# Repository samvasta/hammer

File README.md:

# Hammer

It is tradition for blacksmiths to build their own tools.

In building their tool set, the smith practices their craft and gains a deeper understanding of each tool - what went into its production, how and why it functions. The smith's hammer is built to fit the smith's hands and meet their needs exactly.

The smith's hammer may not make them a better smith, but does make their craft more enjoyable.

I am not a smith, I am a programmer. I work with keyboards and this *my* hammer.

---

This repository contains information about the *hardware*. There may be several different branches to support variations of the hammer.

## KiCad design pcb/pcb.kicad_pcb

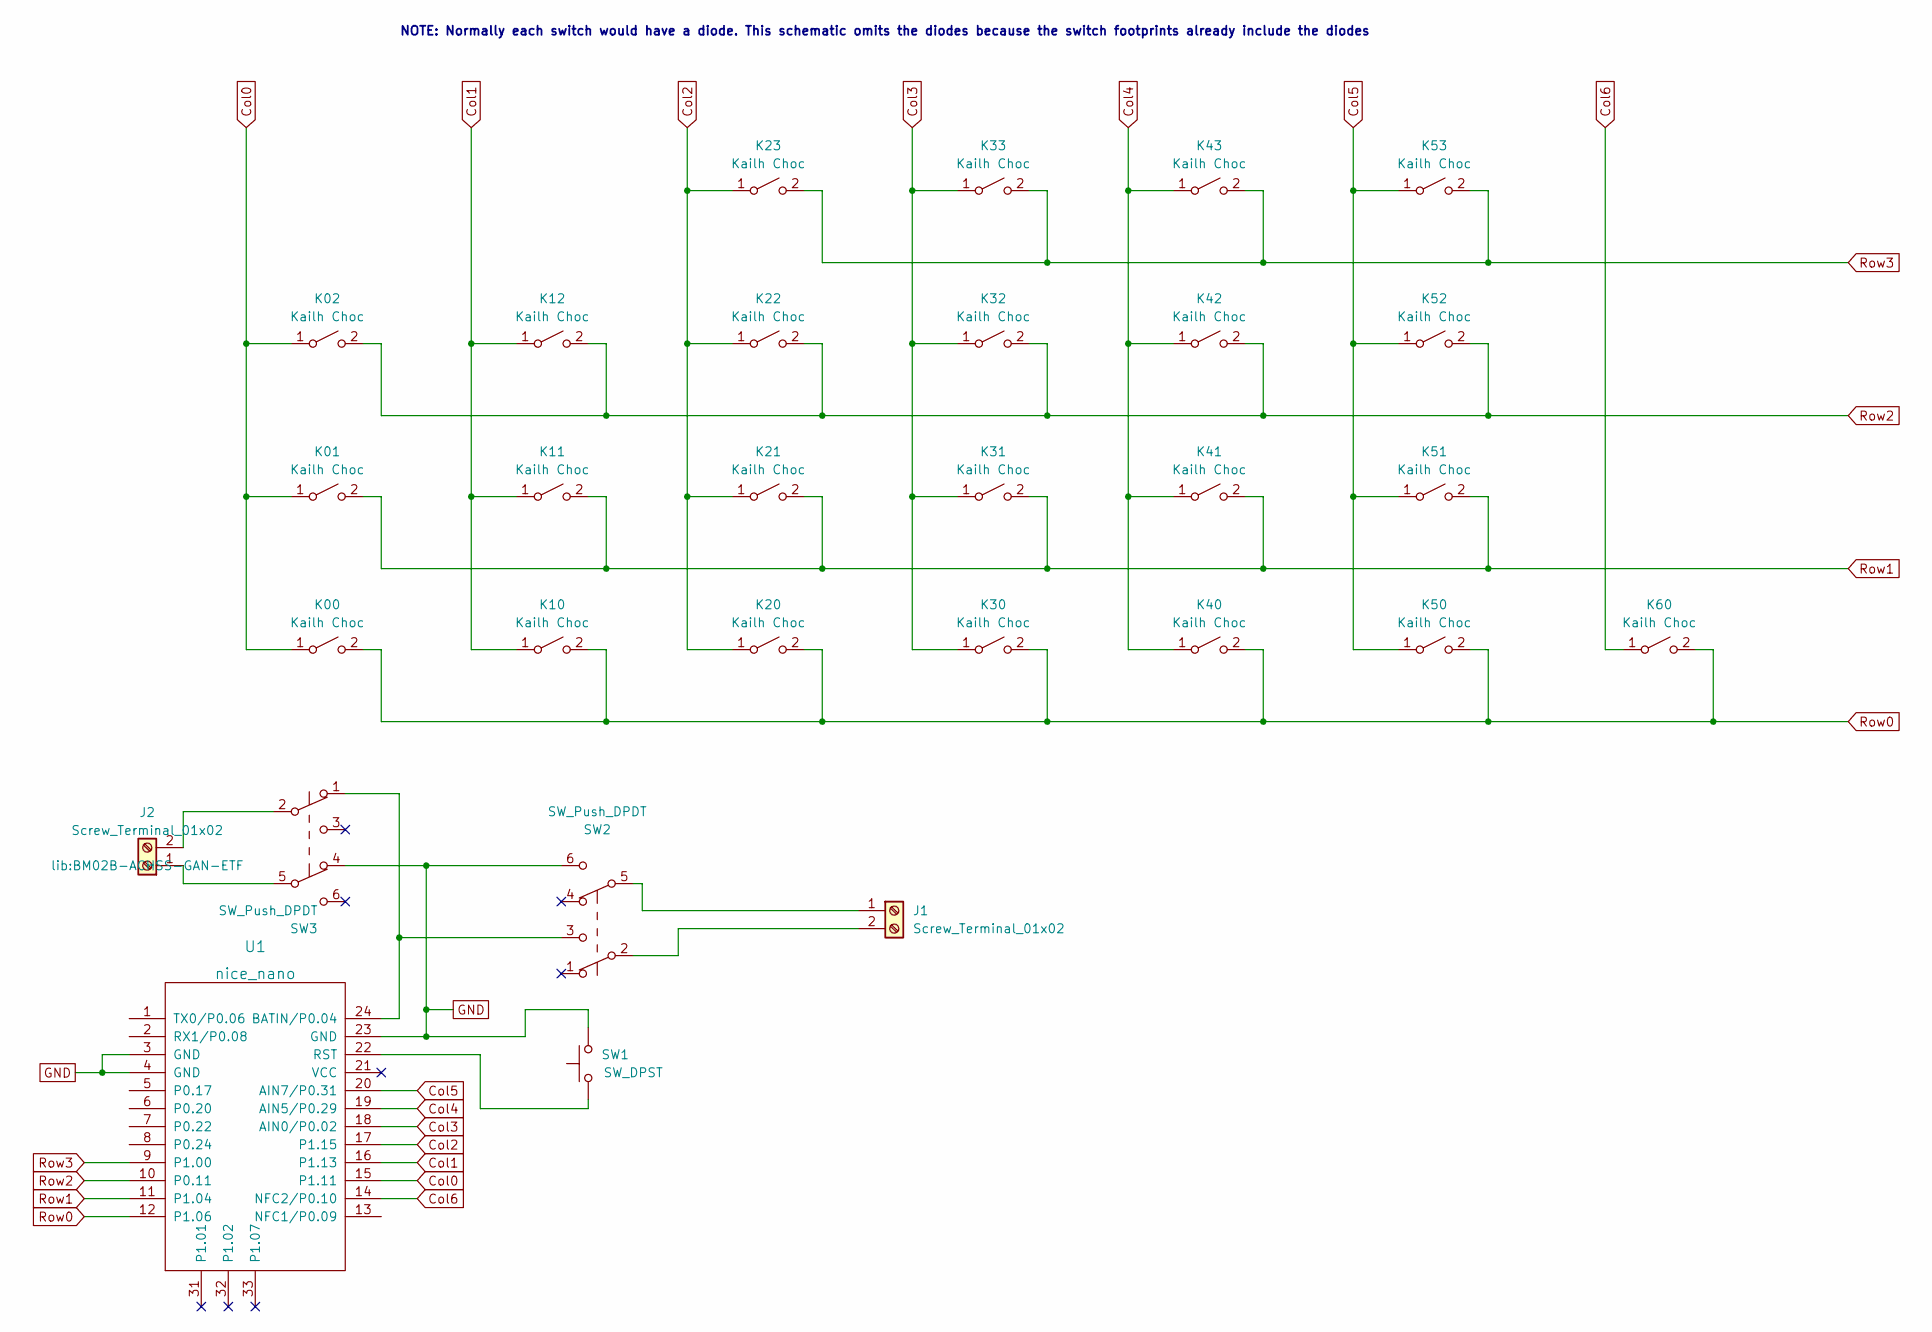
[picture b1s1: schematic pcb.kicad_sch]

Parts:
J1, J2: Screw_Terminal_01x02; BM02B-ACHSS-GAN-ETF
K00, K01, K02, K10, K11, K12, K20, K21, K22, K23, K30, K31, K32, K33, K40, K41, K42, K43, K50, K51, K52, K53, K60: Kailh Choc; Kailh_socket_PG1350_reversible
SW1: SW_DPST; SW_PUSH_6mm
SW2, SW3: SW_Push_DPDT; SW_JS202011SCQN (Reverse Mount)
U1: nice_nano; DIP-24_W15.24mm_Socket

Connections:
Col0: K00.1 (A), K01.1 (A), K02.1 (A), U1.15 (P1.11)
Col1: K10.1 (A), K11.1 (A), K12.1 (A), U1.16 (P1.13)
Col2: K20.1 (A), K21.1 (A), K22.1 (A), K23.1 (A), U1.17 (P1.15)
Col3: K30.1 (A), K31.1 (A), K32.1 (A), K33.1 (A), U1.18 (AIN0/P0.02)
Col4: K40.1 (A), K41.1 (A), K42.1 (A), K43.1 (A), U1.19 (AIN5/P0.29)
Col5: K50.1 (A), K51.1 (A), K52.1 (A), K53.1 (A), U1.20 (AIN7/P0.31)
Col6: K60.1 (A), U1.14 (NFC2/P0.10)
GND: SW1.2, SW2.6 (C), SW3.4 (A), U1.3 (GND), U1.4 (GND), U1.23 (GND)
unnamed: J1.1, SW2.5 (B)
unnamed: J1.2, SW2.2 (B)
unnamed: J2.1, SW3.5 (B)
unnamed: J2.2, SW3.2 (B)
unnamed: SW1.1, U1.22 (RST)
unnamed: SW2.3 (C), SW3.1 (A), U1.24 (BATIN/P0.04)
Row0: K00.2 (B), K10.2 (B), K20.2 (B), K30.2 (B), K40.2 (B), K50.2 (B), K60.2 (B), U1.12 (P1.06)
Row1: K01.2 (B), K11.2 (B), K21.2 (B), K31.2 (B), K41.2 (B), K51.2 (B), U1.11 (P1.04)
Row2: K02.2 (B), K12.2 (B), K22.2 (B), K32.2 (B), K42.2 (B), K52.2 (B), U1.10 (P0.11)
Row3: K23.2 (B), K33.2 (B), K43.2 (B), K53.2 (B), U1.9 (P1.00)

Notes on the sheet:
NOTE: Normally each switch would have a diode. This schematic omits the diodes because the switch footprints already include the diodes

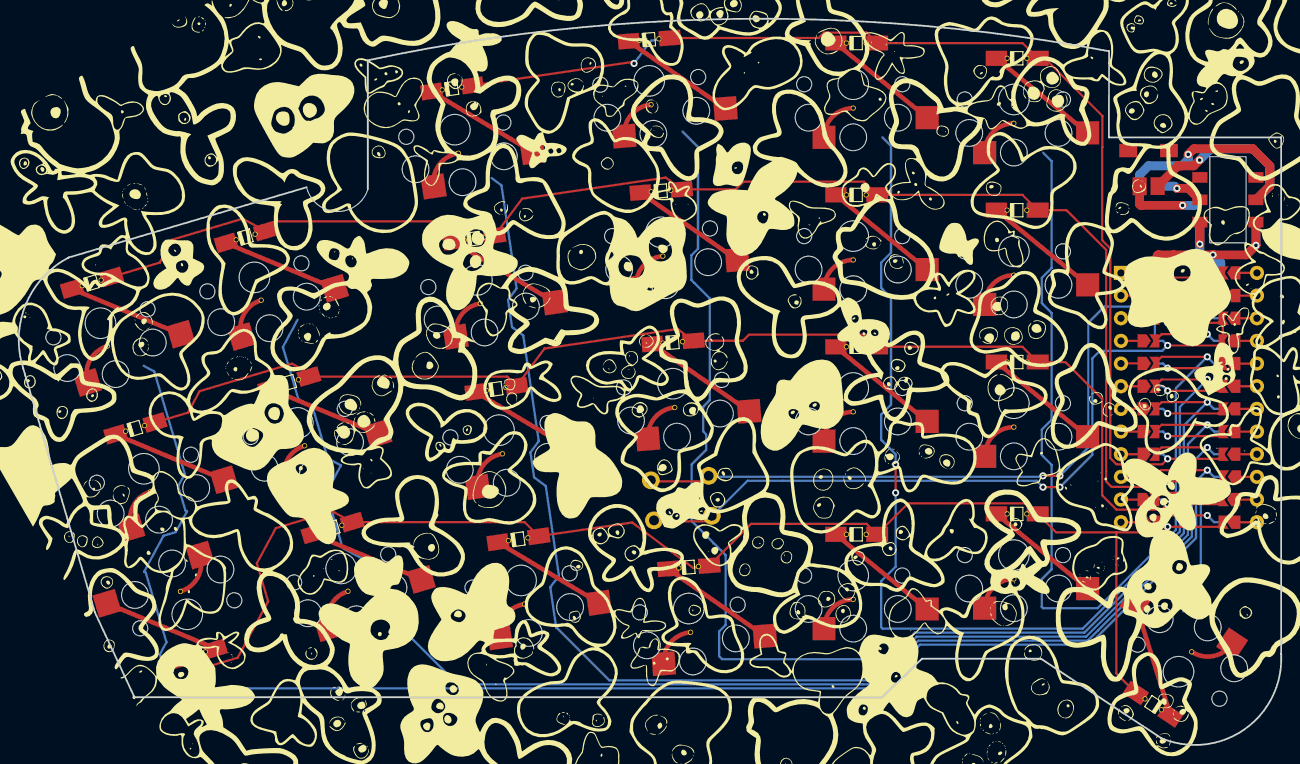
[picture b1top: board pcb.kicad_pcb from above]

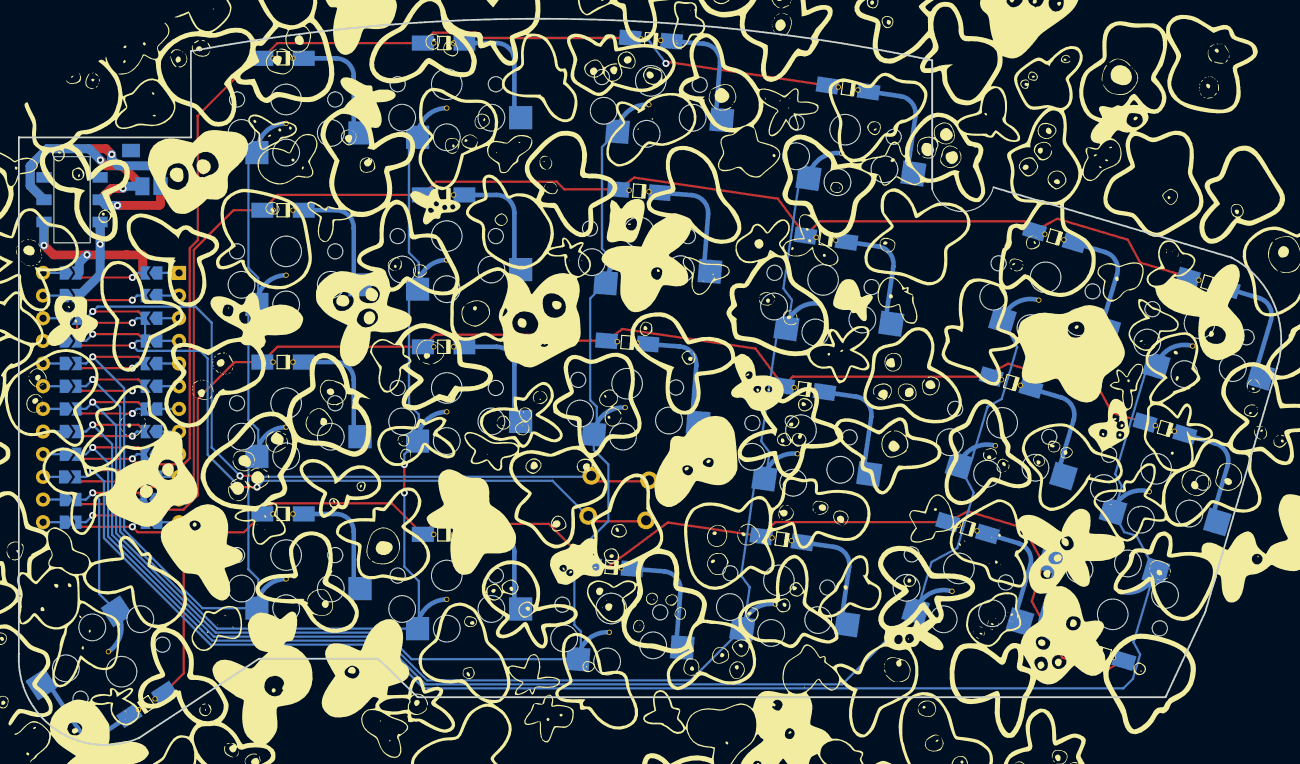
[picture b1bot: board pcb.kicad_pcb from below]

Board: 2 copper layers, 141.5 x 81.4 mm, 29 parts (3 on the bottom side), 18 nets.

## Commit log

2023-05-13 init kicad project & start on layout
2023-05-13 layout
2023-05-13 more layout changes
2023-05-13 nice shape
2023-05-14 first pass at pcb and case
2023-05-20 refining the shape
2023-05-23 playing around with layouts & shapes
2023-05-24 update pcb for new shape
2023-05-27 update pcb
2023-05-27 update project to kicad 7
2023-05-27 switch to low-profile battery connector
2023-05-28 update pcb for low pro battery connector
2023-05-29 update case models
2023-06-03 pcb v1
